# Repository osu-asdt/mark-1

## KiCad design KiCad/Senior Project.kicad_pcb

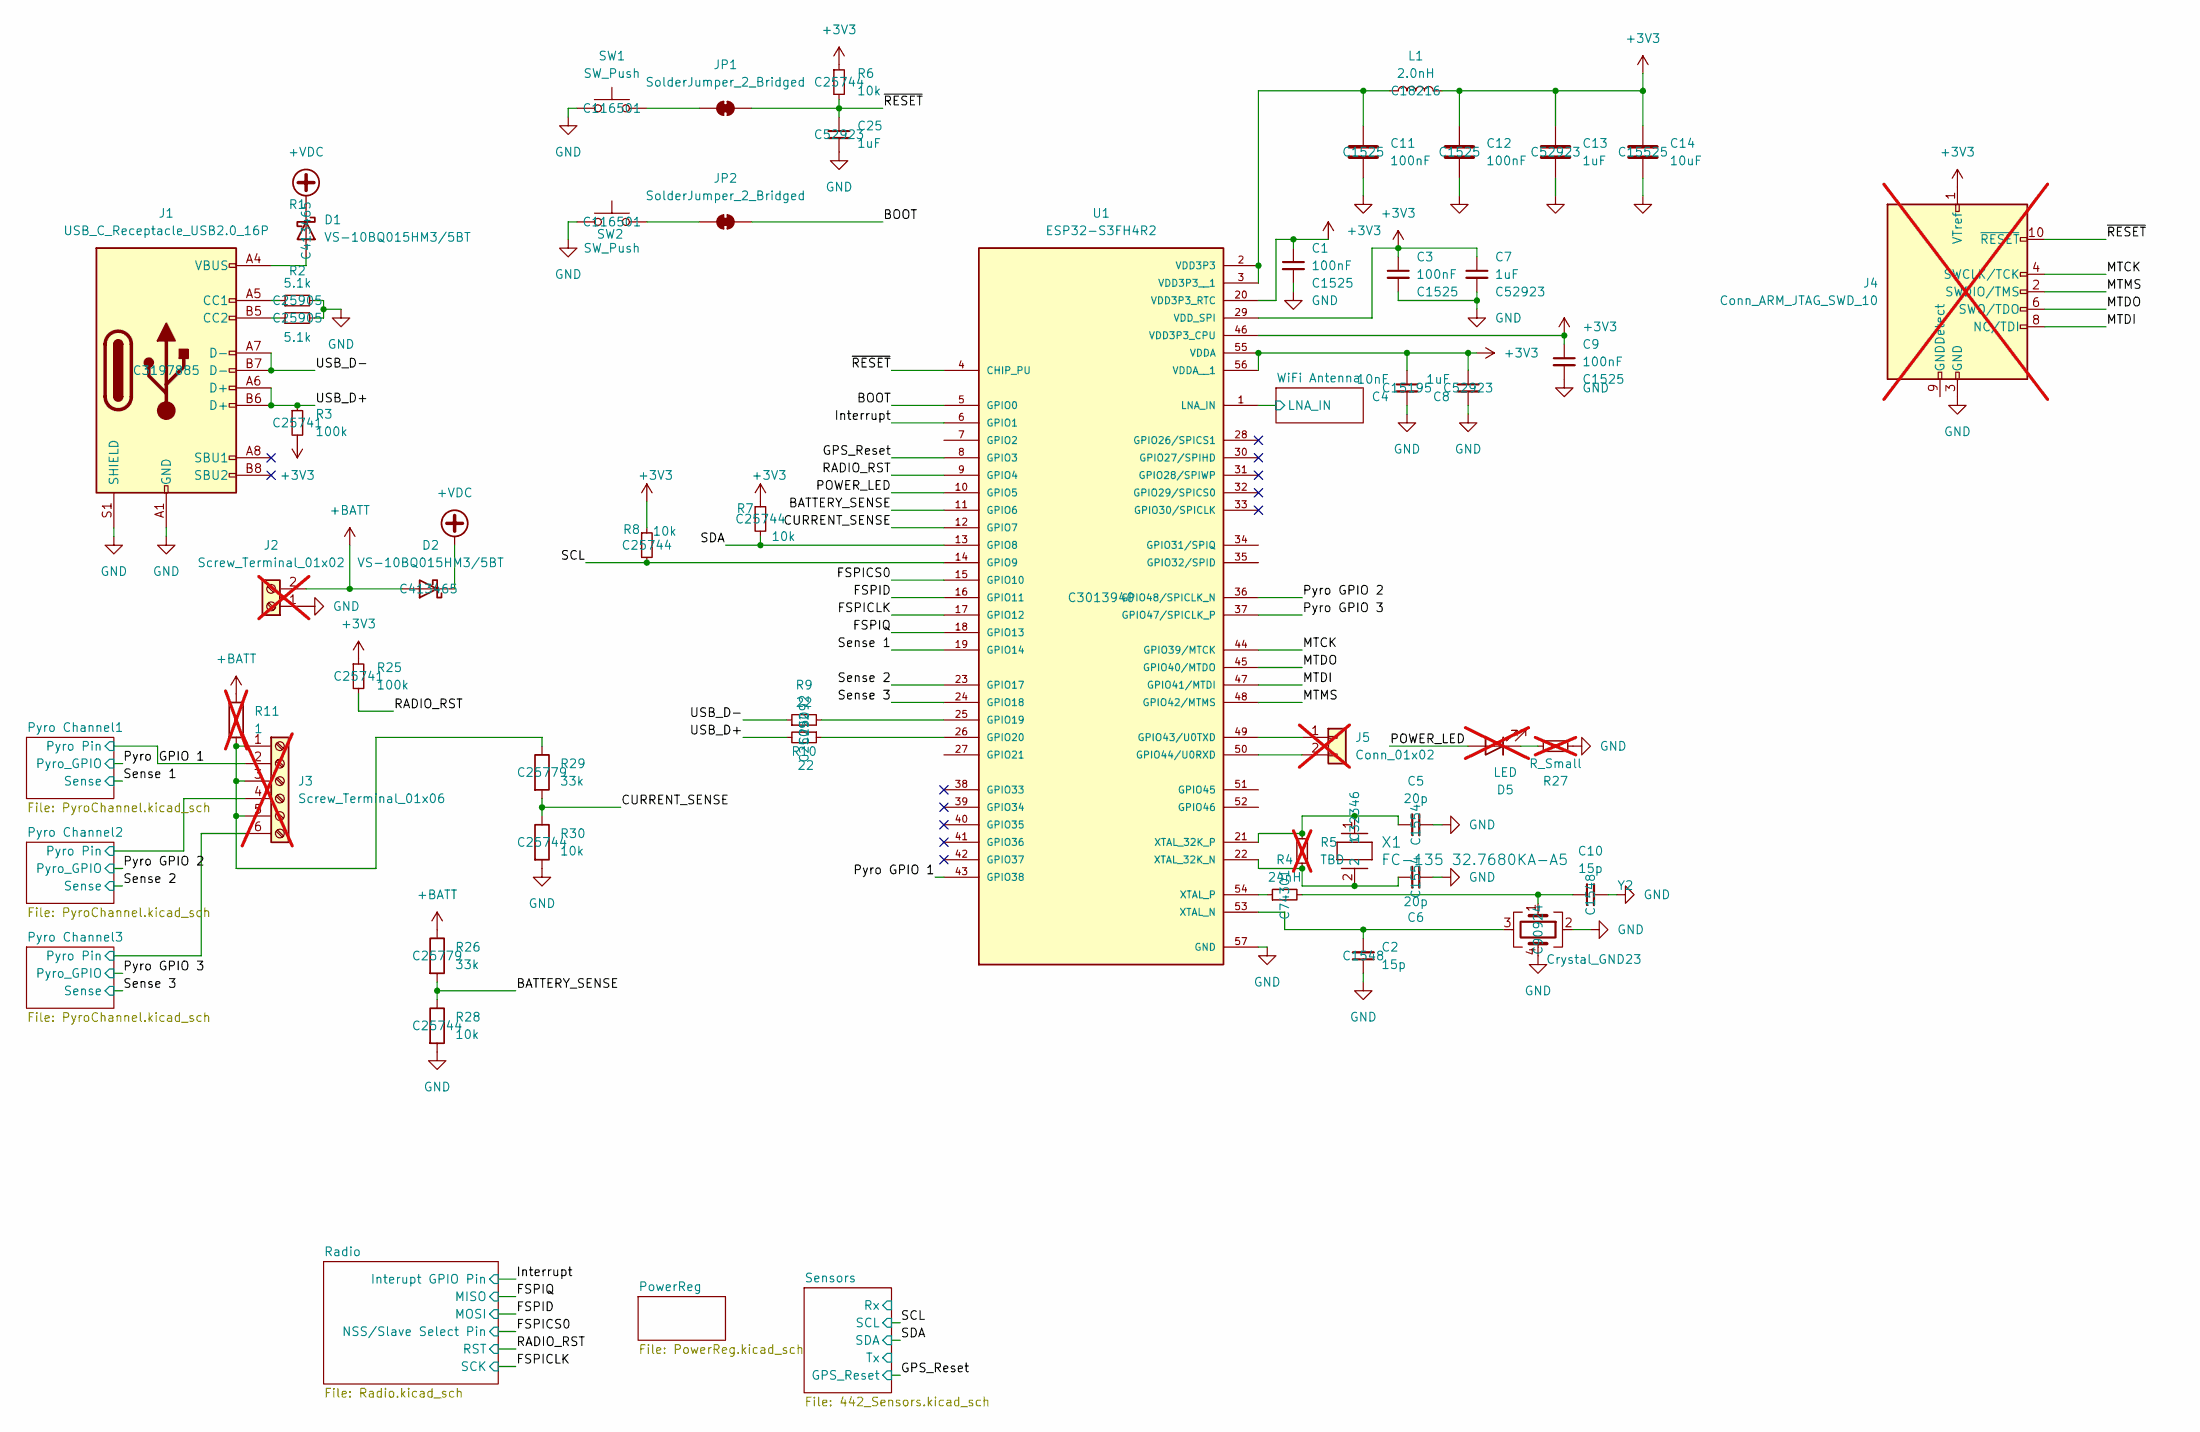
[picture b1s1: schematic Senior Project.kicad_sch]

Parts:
C1, C3, C9, C11, C12: 100nF; C_0402_1005Metric; LCSC C1525
C2, C10: 15p; C_0402_1005Metric; LCSC C1548
C4: 10nF; C_0402_1005Metric; LCSC C15195
C5, C6: 20p; C_0402_1005Metric; LCSC C1554
C7, C8, C13, C25: 1uF; C_0402_1005Metric; LCSC C52923
C14: 10uF; C_0402_1005Metric; LCSC C15525
D1, D2: VS-10BQ015HM3/5BT; D_SMB; LCSC C413465
D5: LED; LED_0603_1608Metric; not fitted
J1: USB_C_Receptacle_USB2.0_16P; USB_C_Receptacle_G-Switch_GT-USB-7010ASV; LCSC C3197885
J2: Screw_Terminal_01x02; CONN_OSTVN02A150_OST; not fitted
J3: Screw_Terminal_01x06; CONN_OSTVN06A150_OST; not fitted
J4: Conn_ARM_JTAG_SWD_10; PinHeader_2x05_P1.27mm_Vertical_SMD; not fitted
J5: Conn_01x02; PinHeader_1x02_P1.27mm_Vertical_SMD_Pin1Right; not fitted
JP1, JP2: SolderJumper_2_Bridged; SolderJumper-2_P1.3mm_Bridged_RoundedPad1.0x1.5mm
L1: 2.0nH; L_0402_1005Metric; LCSC C18216
R1, R2: 5.1k; R_0402_1005Metric; LCSC C25905
R3, R25: 100k; R_0402_1005Metric; LCSC C25741
R4: 24nH; C_0402_1005Metric; LCSC C74301
R5: TBD; C_0402_1005Metric; not fitted
R6, R7, R8, R28, R30: 10k; R_0402_1005Metric; LCSC C25744
R9, R10: 22; R_0402_1005Metric; LCSC C25092
R11: 1; R_2512_6332Metric; not fitted
R26, R29: 33k; R_0402_1005Metric; LCSC C25779
R27: R_Small; R_0603_1608Metric; not fitted
SW1, SW2: SW_Push; SW_SPST_PTS810; LCSC C116501
U1: ESP32-S3FH4R2; QFN40P700X700X90-57N; PARTREV 1.8mm; LCSC C3013940
X1: FC-135 32.7680KA-A5; XTAL_FC-135_EPS; LCSC C32346
Y2: Crystal_GND23; Crystal_SMD_3225-4Pin_3.2x2.5mm; LCSC C90924

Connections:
+3V3: C1.1, C3.1, C4.1, C7.1, C8.1, C9.1, C12.1, C13.1, C14.1, J4.1 (VTref), L1.2, R3.2, R6.1, R7.1, R8.1, R25.1, U1.20 (VDD3P3_RTC), U1.29 (VDD_SPI), U1.46 (VDD3P3_CPU), U1.55 (VDDA), U1.56 (VDDA__1); also elsewhere on the board
+BATT: D2.2 (A), J2.2, R11.1, R26.1
+VDC: D1.1 (K), D2.1 (K); also elsewhere on the board
/BATTERY_SENSE: R26.2, R28.1, U1.11 (GPIO6)
/BOOT: JP2.2 (B), U1.5 (GPIO0)
/CURRENT_SENSE: R29.2, R30.1, U1.12 (GPIO7)
/FSPICLK: U1.17 (GPIO12); also elsewhere on the board
/FSPICS0: U1.15 (GPIO10); also elsewhere on the board
/FSPID: U1.16 (GPIO11); also elsewhere on the board
/FSPIQ: U1.18 (GPIO13); also elsewhere on the board
/GPS_Reset: U1.8 (GPIO3); also elsewhere on the board
/Interrupt: U1.6 (GPIO1); also elsewhere on the board
/MTCK: J4.4 (SWCLK/TCK), U1.44 (GPIO39/MTCK)
/MTDI: J4.8 (NC/TDI), U1.47 (GPIO41/MTDI)
/MTDO: J4.6 (SWO/TDO), U1.45 (GPIO40/MTDO)
/MTMS: J4.2 (SWDIO/TMS), U1.48 (GPIO42/MTMS)
/POWER_LED: D5.2 (A), U1.10 (GPIO5)
/Pyro Channel1/Pyro Pin: J3.2; also elsewhere on the board
/Pyro Channel2/Pyro Pin: J3.4; also elsewhere on the board
/Pyro Channel3/Pyro Pin: J3.6; also elsewhere on the board
/Pyro GPIO 1: U1.43 (GPIO38); also elsewhere on the board
/Pyro GPIO 2: U1.36 (GPIO48/SPICLK_N); also elsewhere on the board
/Pyro GPIO 3: U1.37 (GPIO47/SPICLK_P); also elsewhere on the board
/RADIO_RST: R25.2, U1.9 (GPIO4); also elsewhere on the board
/SCL: R8.2, U1.14 (GPIO9); also elsewhere on the board
/SDA: R7.2, U1.13 (GPIO8); also elsewhere on the board
/Sense 1: U1.19 (GPIO14); also elsewhere on the board
/Sense 2: U1.23 (GPIO17); also elsewhere on the board
/Sense 3: U1.24 (GPIO18); also elsewhere on the board
/USB_D+: J1.A6 (D+), J1.B6 (D+), R3.1, R10.2
/USB_D-: J1.A7 (D-), J1.B7 (D-), R9.1
/WiFi Antenna/LNA_IN: U1.1 (LNA_IN); also elsewhere on the board
/~ACCELEROMETER_CS: U1.7 (GPIO2); also elsewhere on the board
/~GYRO_CS: U1.27 (GPIO21); also elsewhere on the board
/~RESET: C25.1, J4.10 (~RESET), JP1.2 (B), R6.2, U1.4 (CHIP_PU)
GND: C1.2, C2.1, C3.2, C4.2, C5.2, C6.2, C7.2, C8.2, C9.2, C10.2, C11.2, C12.2, C13.2, C14.2, C25.2, J1.A1 (GND), J1.A12 (GND), J1.B1 (GND), J1.B12 (GND), J1.S1 (SHIELD), J2.1, J4.3 (GND), J4.5 (GND), R1.2, R2.2, R27.2, R28.2, R30.2, SW1.1, SW2.1, U1.57 (GND), Y2.2, Y2.4; also elsewhere on the board
unnamed: C10.1, R4.2, Y2.1
unnamed: D1.2 (A), J1.A4 (VBUS), J1.A9 (VBUS), J1.B4 (VBUS), J1.B9 (VBUS)
unnamed: D5.1 (K), R27.1
unnamed: J1.A5 (CC1), R1.1
unnamed: J1.B5 (CC2), R2.1
unnamed: J3.1, J3.3, J3.5, R11.2, R29.1
unnamed: J5.1, U1.49 (GPIO43/U0TXD)
unnamed: J5.2, U1.50 (GPIO44/U0RXD)
unnamed: JP1.1 (A), SW1.2
unnamed: JP2.1 (A), SW2.2
unnamed: R9.2, U1.25 (GPIO19)
unnamed: R10.1, U1.26 (GPIO20)
unnamed: C11.1, L1.1, U1.2 (VDD3P3), U1.3 (VDD3P3__1)
unnamed: C6.1, R5.2, U1.22 (XTAL_32K_N), X1.2
unnamed: C5.1, R5.1, U1.21 (XTAL_32K_P), X1.1
unnamed: C2.2, U1.53 (XTAL_N), Y2.3
unnamed: R4.1, U1.54 (XTAL_P)

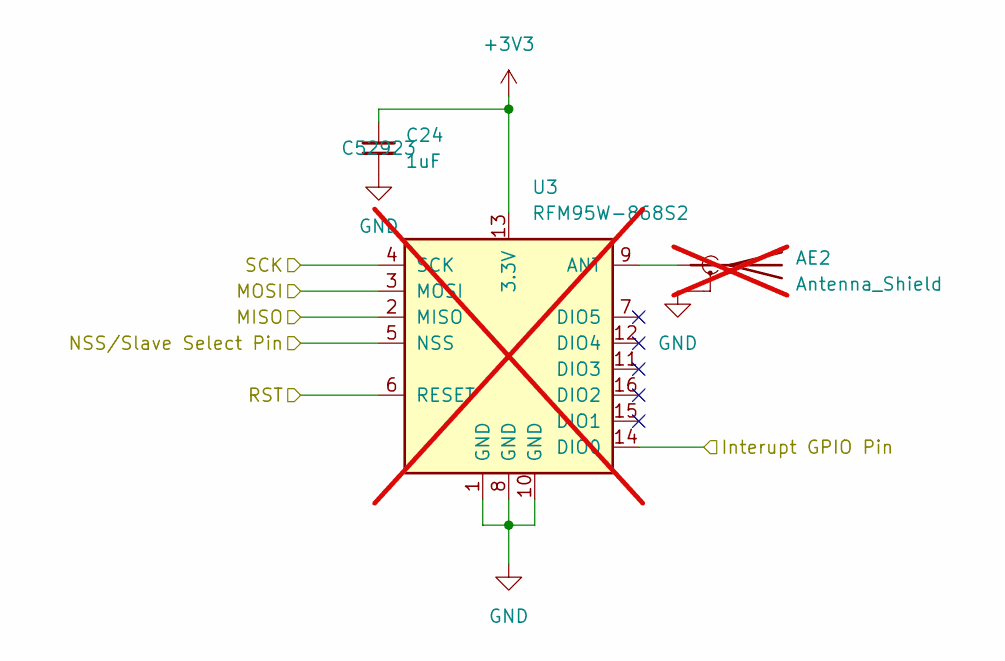
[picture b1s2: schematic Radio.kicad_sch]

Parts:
AE2: Antenna_Shield; SMA_Samtec_SMA-J-P-H-ST-EM1_EdgeMount; not fitted
C24: 1uF; C_0402_1005Metric; LCSC C52923
U3: RFM95W-868S2; HOPERF_RFM9XW_SMD; not fitted

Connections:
+3V3: C24.1, U3.13 (3.3V); also elsewhere on the board
/FSPICLK: U3.4 (SCK); also elsewhere on the board
/FSPICS0: U3.5 (NSS); also elsewhere on the board
/FSPID: U3.3 (MOSI); also elsewhere on the board
/FSPIQ: U3.2 (MISO); also elsewhere on the board
/Interrupt: U3.14 (DIO0); also elsewhere on the board
/RADIO_RST: U3.6 (RESET); also elsewhere on the board
GND: AE2.2 (Shield), C24.2, U3.1 (GND), U3.8 (GND), U3.10 (GND); also elsewhere on the board
unnamed: AE2.1 (A), U3.9 (ANT)

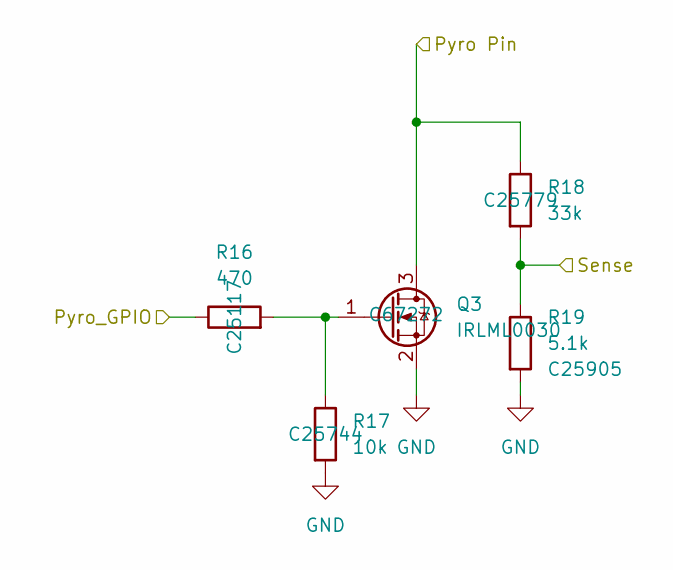
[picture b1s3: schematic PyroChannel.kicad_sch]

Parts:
Q3: IRLML0030; SOT-23; LCSC C67272
R16: 470; R_0402_1005Metric; LCSC C25117
R17: 10k; R_0402_1005Metric; LCSC C25744
R18: 33k; R_0402_1005Metric; LCSC C25779
R19: 5.1k; R_0402_1005Metric; LCSC C25905

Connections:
/Pyro Channel2/Pyro Pin: Q3.3 (D), R18.1; also elsewhere on the board
/Pyro GPIO 2: R16.1; also elsewhere on the board
/Sense 2: R18.2, R19.1; also elsewhere on the board
GND: Q3.2 (S), R17.2, R19.2; also elsewhere on the board
unnamed: Q3.1 (G), R16.2, R17.1

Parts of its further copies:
Q2, Q4: IRLML0030; SOT-23; LCSC C67272
R12, R20: 470; R_0402_1005Metric; LCSC C25117
R13, R21: 10k; R_0402_1005Metric; LCSC C25744
R14, R22: 33k; R_0402_1005Metric; LCSC C25779
R15, R23: 5.1k; R_0402_1005Metric; LCSC C25905

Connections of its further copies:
/Pyro Channel1/Pyro Pin: Q2.3 (D), R14.1; also elsewhere on the board
/Pyro Channel3/Pyro Pin: Q4.3 (D), R22.1; also elsewhere on the board
/Pyro GPIO 1: R12.1; also elsewhere on the board
/Pyro GPIO 3: R20.1; also elsewhere on the board
/Sense 1: R14.2, R15.1; also elsewhere on the board
/Sense 3: R22.2, R23.1; also elsewhere on the board
GND: Q2.2 (S), Q4.2 (S), R13.2, R15.2, R21.2, R23.2; also elsewhere on the board
unnamed: Q2.1 (G), R12.2, R13.1
unnamed: Q4.1 (G), R20.2, R21.1

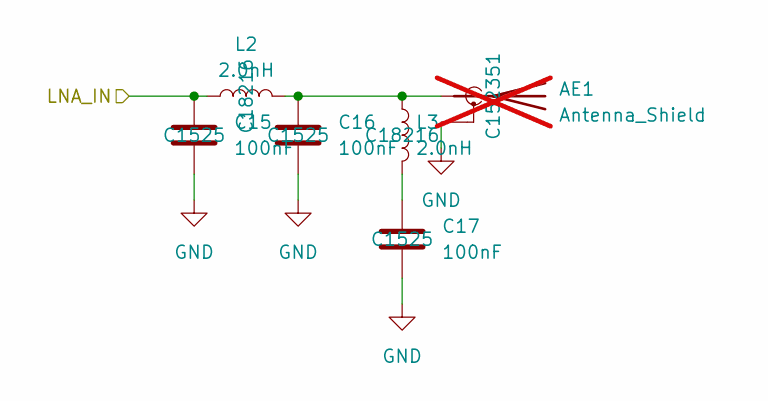
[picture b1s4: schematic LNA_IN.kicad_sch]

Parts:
AE1: Antenna_Shield; Molex_47948-0001_2.4Ghz; LCSC C152351; not fitted
C15, C16, C17: 100nF; C_0402_1005Metric; LCSC C1525
L2, L3: 2.0nH; L_0402_1005Metric; LCSC C18216

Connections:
/WiFi Antenna/LNA_IN: C15.1, L2.1; also elsewhere on the board
GND: AE1.2 (Shield), C15.2, C16.2, C17.2; also elsewhere on the board
unnamed: AE1.1 (A), C16.1, L2.2, L3.1
unnamed: C17.1, L3.2

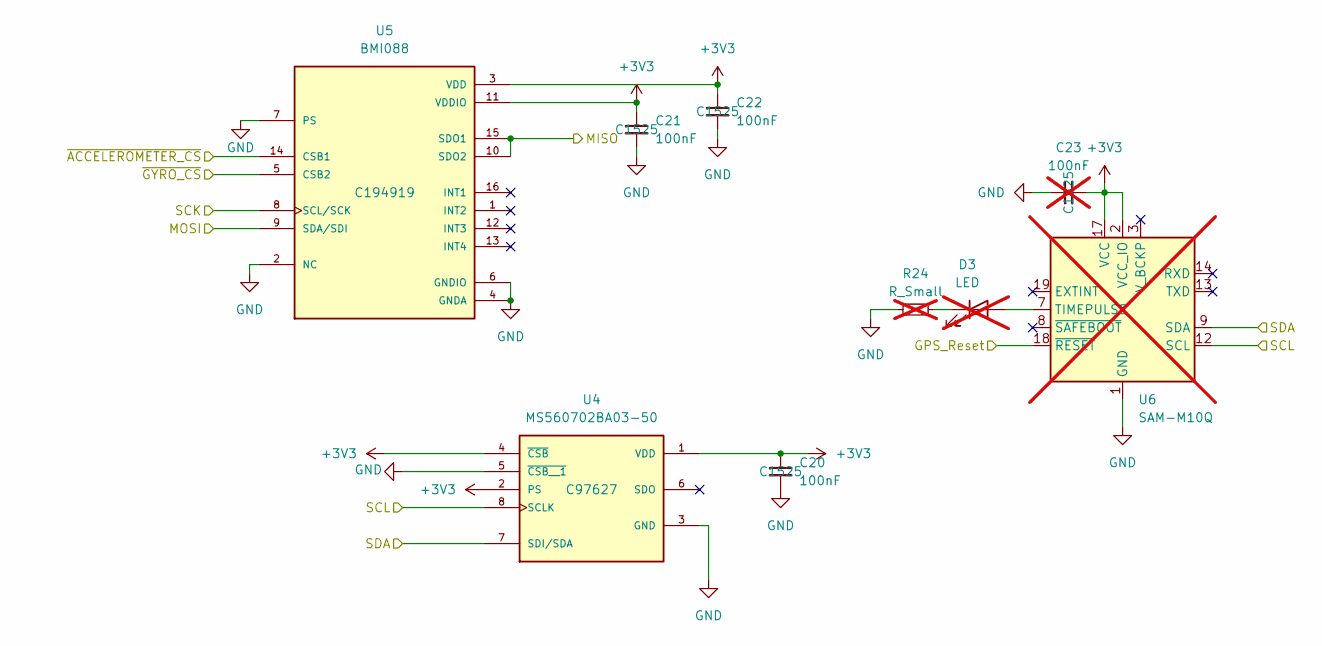
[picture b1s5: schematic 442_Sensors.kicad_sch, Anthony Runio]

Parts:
C20, C21, C22: 100nF; C_0402_1005Metric; LCSC C1525
C23: 100nF; C_0402_1005Metric; LCSC C1525; not fitted
D3: LED; LED_0603_1608Metric; not fitted
R24: R_Small; R_0603_1608Metric; not fitted
U4: MS560702BA03-50; SON8_MS5611_TEC; LCSC C97627
U5: BMI088; PQFN50P450X300X100-16N; LCSC C194919
U6: SAM-M10Q; ublox_SAM-M8Q; not fitted

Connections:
+3V3: C20.1, C21.1, C22.1, C23.2, U4.1 (VDD), U4.2 (PS), U4.4 (~CSB), U5.3 (VDD), U5.11 (VDDIO), U6.2 (VCC_IO), U6.17 (VCC); also elsewhere on the board
/FSPICLK: U5.8 (SCL/SCK); also elsewhere on the board
/FSPID: U5.9 (SDA/SDI); also elsewhere on the board
/FSPIQ: U5.10 (SDO2), U5.15 (SDO1); also elsewhere on the board
/GPS_Reset: U6.18 (~RESET); also elsewhere on the board
/SCL: U4.8 (SCLK), U6.12 (SCL); also elsewhere on the board
/SDA: U4.7 (SDI/SDA), U6.9 (SDA); also elsewhere on the board
/~ACCELEROMETER_CS: U5.14 (CSB1); also elsewhere on the board
/~GYRO_CS: U5.5 (CSB2); also elsewhere on the board
GND: C20.2, C21.2, C22.2, C23.1, R24.2, U4.3 (GND), U4.5 (~CSB__1), U5.2 (NC), U5.4 (GNDA), U5.6 (GNDIO), U5.7 (PS), U6.1 (GND), U6.4 (GND), U6.5 (GND), U6.6 (GND), U6.10 (GND), U6.11 (GND), U6.15 (GND), U6.16 (GND), U6.20 (GND); also elsewhere on the board
unnamed: D3.2 (A), U6.7 (TIMEPULSE)
unnamed: D3.1 (K), R24.1

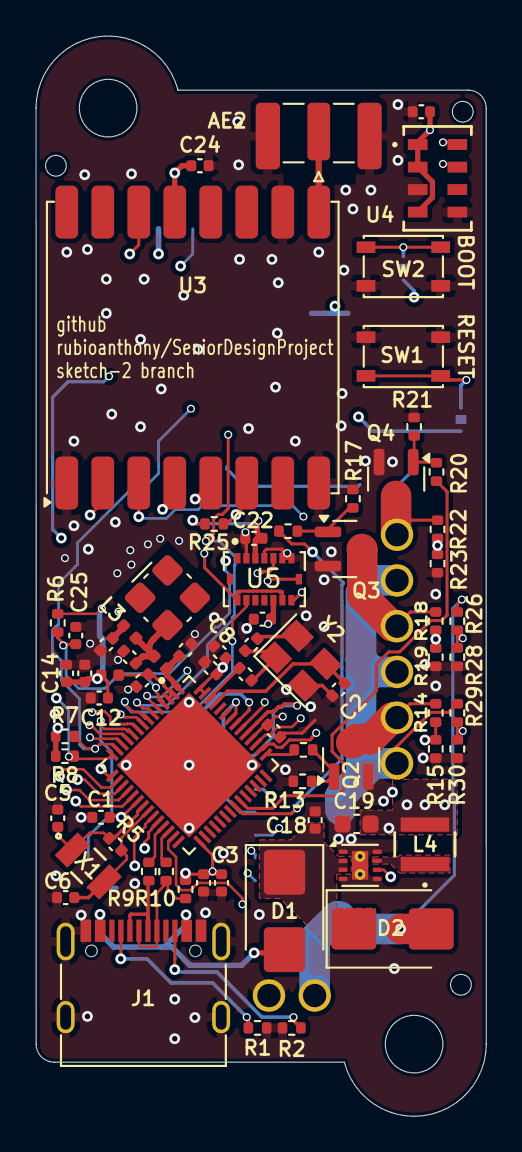
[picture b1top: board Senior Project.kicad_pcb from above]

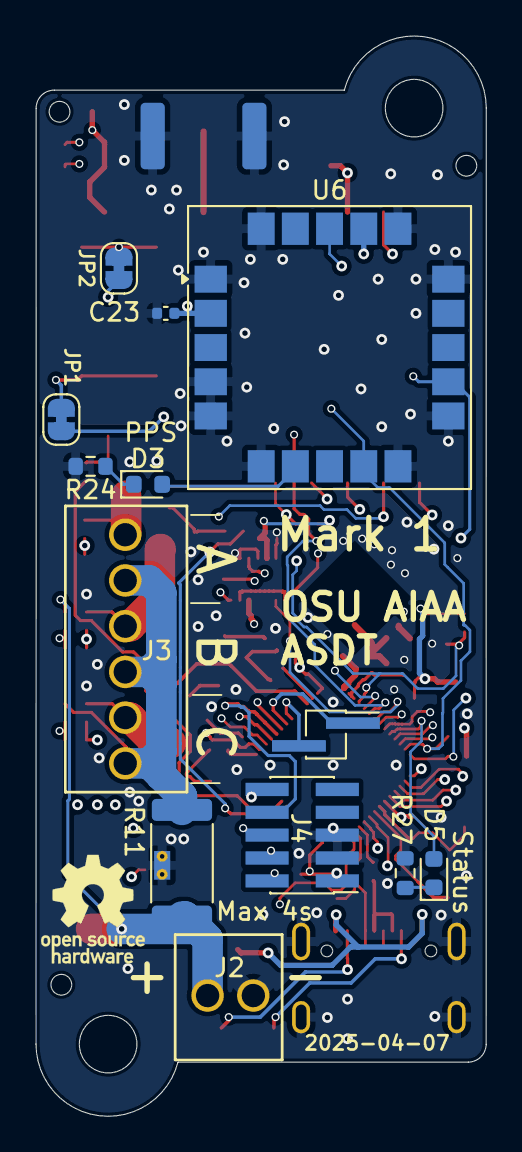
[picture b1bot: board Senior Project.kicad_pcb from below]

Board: 4 copper layers, 25.0 x 60.0 mm, 85 parts (13 on the bottom side), 62 nets.

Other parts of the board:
C18: 10uF; C_0402_1005Metric
C19: 22uF; C_0603_1608Metric
L4: 2.2uH; IND_TAIYO_NR3015_TAY
U2: TPS62162DSG; WSON-8-1EP_2x2mm_P0.5mm_EP0.9x1.6mm_ThermalVias

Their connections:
+3V3: C19.1, L4.2, U2.6 (VOS); also elsewhere on the board
+VDC: C18.1, U2.2 (VIN), U2.3 (EN); also elsewhere on the board
GND: C18.2, C19.2, U2.1 (PGND), U2.4 (AGND), U2.5 (FB), U2.8 (PG), U2.9 (PAD); also elsewhere on the board
unnamed: L4.1, U2.7 (SW)

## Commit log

2025-04-06 fixed DRC rules, more silkscreen work
2025-04-06 adjustments to work with JLC and to match with example
2025-04-06 prepare to move barometer to front
2025-04-06 move barometer to front
2025-04-06 add JLC assembly tooling holes
2025-04-06 finalize board
2025-04-06 ready to send out
2025-04-07 further tweaks
2025-04-07 3d model fixes
2025-04-07 clean up schematic, add voltage dividers for measuring battery and charge firing current
2025-04-07 finalize layout, again
2025-04-07 ordering, for real this time
2025-04-07 switch to BMI088 for IMU
2025-04-08 further refine board
2025-04-08 add OSHW logo
2025-04-08 sent to fab
2025-05-31 move code to another repo
2025-05-31 rename project
